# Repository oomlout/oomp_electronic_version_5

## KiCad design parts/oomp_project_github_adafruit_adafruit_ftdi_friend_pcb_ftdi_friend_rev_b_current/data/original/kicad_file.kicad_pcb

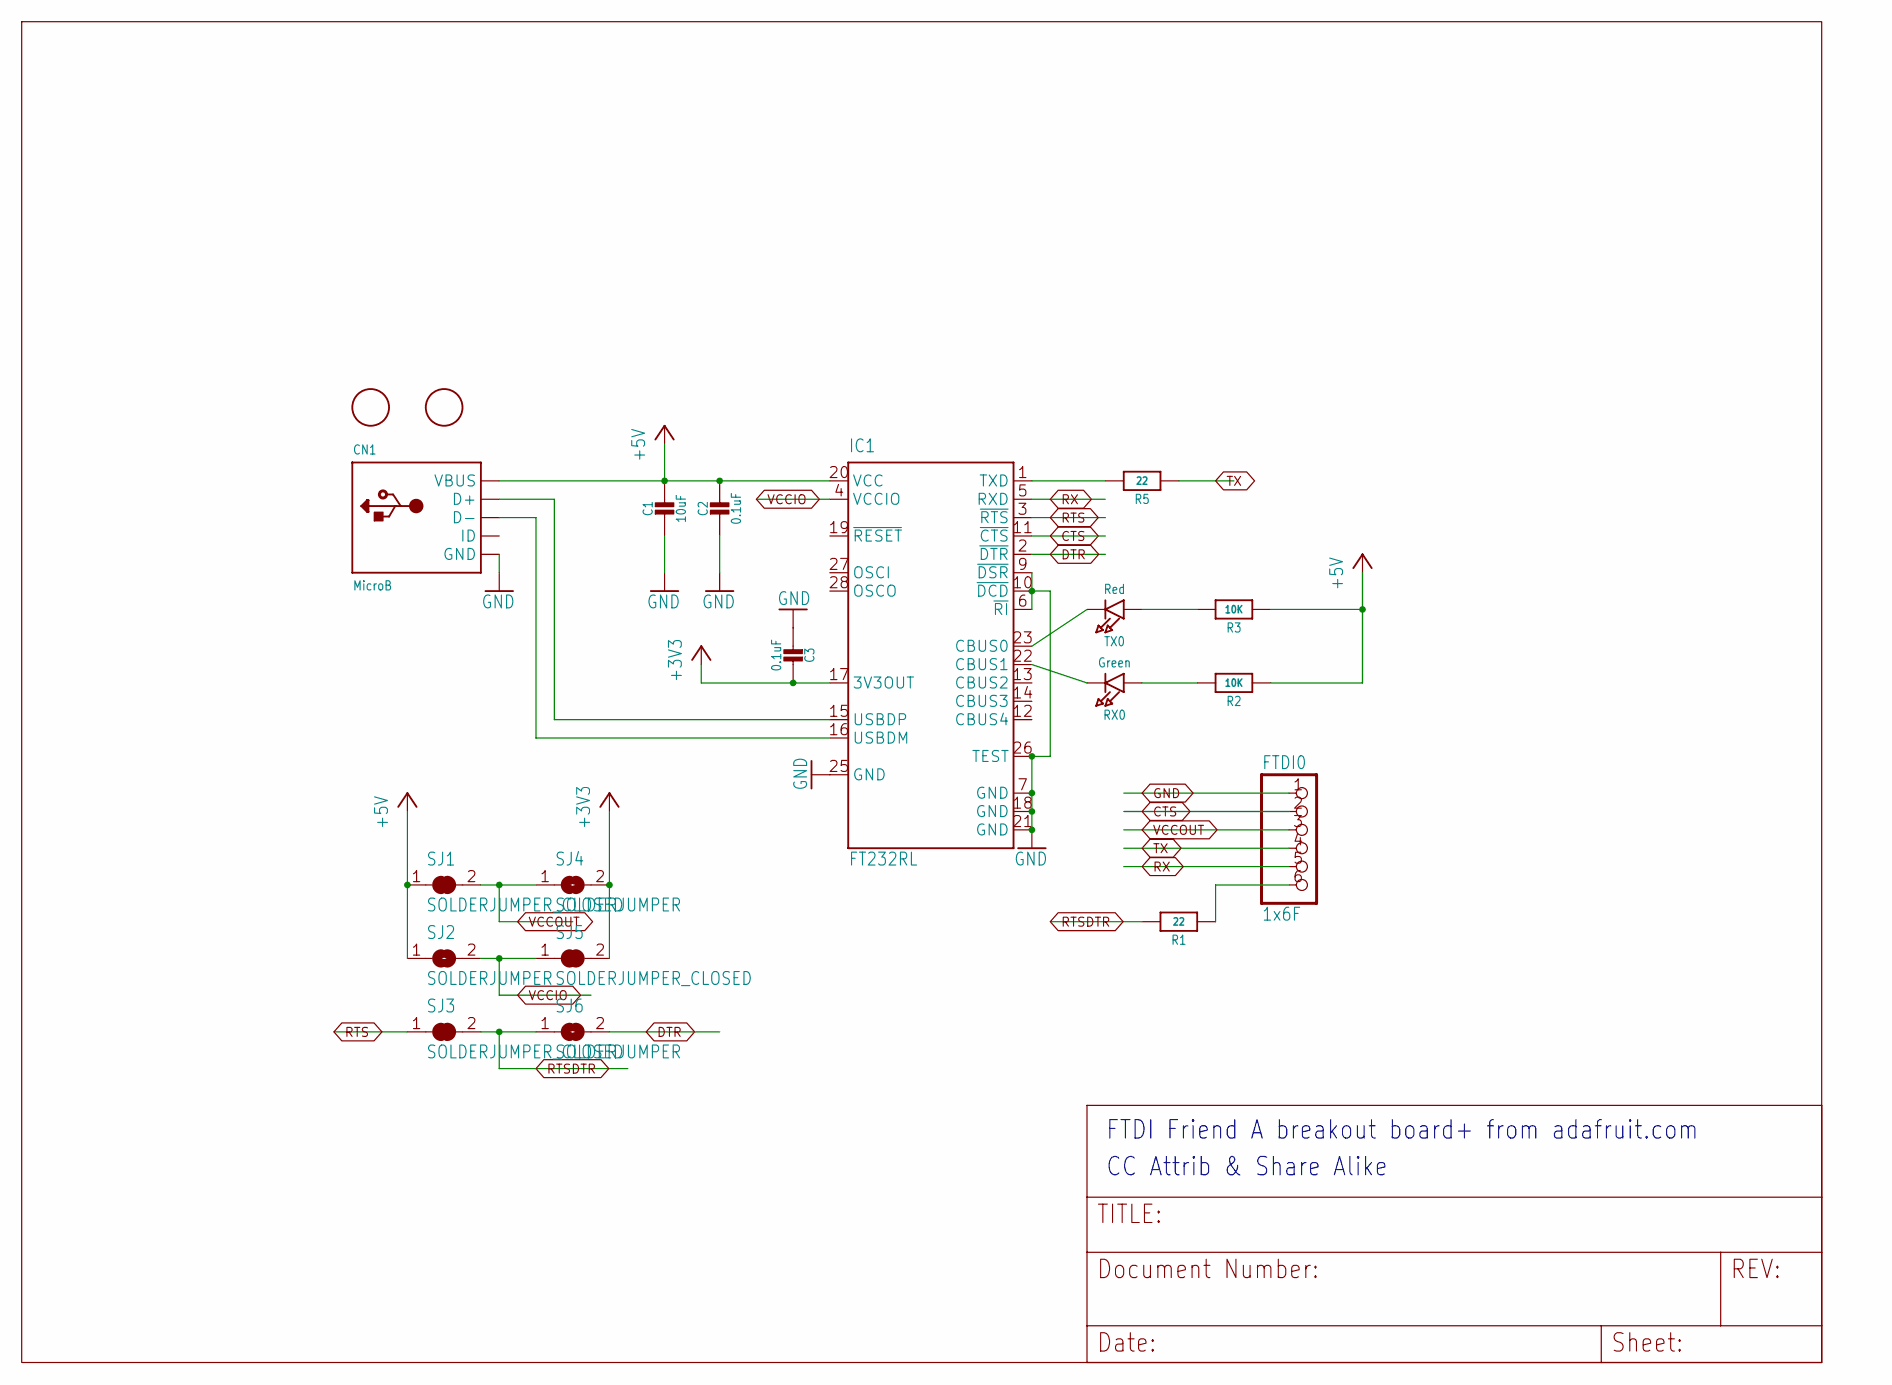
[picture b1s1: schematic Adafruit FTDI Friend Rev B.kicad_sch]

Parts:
C1: 10uF; 0805-NO
C2, C3: 0.1uF; 0603-NO
CN1: MicroB; SHOU_MICROXNJ073; LCSC C404969
FTDI0: 1x6F; 1X06-CLEANBIG
IC1: FT232RL; SSOP28; MPN FT232RL
R1, R5: 22; 0603-NO
R2, R3: 10K; 0603-NO
RX0: Green; CHIPLED_0603_NOOUTLINE
SJ1, SJ3, SJ5: SOLDERJUMPER_CLOSED; SOLDERJUMPER_CLOSEDWIRE
SJ2, SJ4, SJ6: SOLDERJUMPER; SOLDERJUMPER_ARROW_NOPASTE
TX0: Red; CHIPLED_0603_NOOUTLINE
U$1, U$2: FIDUCIAL; FIDUCIAL_1MM

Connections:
+3V3: C3.1, IC1.17 (3V3OUT), SJ4.2, SJ5.2
+5V: C1.1, C2.1, CN1.VBUS, IC1.20 (VCC), R2.1, R3.1, SJ1.1, SJ2.1
CTS: FTDI0.2, IC1.11 (~CTS)
DTR: IC1.2 (~DTR), SJ6.2
GND: C1.2, C2.2, C3.2, CN1.BASE@1 (GND), CN1.BASE@2 (GND), CN1.GND, CN1.SPRT@1 (GND), CN1.SPRT@2 (GND), CN1.SPRT@3 (GND), CN1.SPRT@4 (GND), FTDI0.1, IC1.6 (~RI), IC1.7 (GND), IC1.9 (~DSR), IC1.10 (~DCD), IC1.18 (GND), IC1.21 (GND), IC1.25 (GND), IC1.26 (TEST)
unnamed: FTDI0.6, R1.1
unnamed: CN1.D+, IC1.15 (USBDP)
unnamed: CN1.D-, IC1.16 (USBDM)
unnamed: IC1.1 (TXD), R5.2
unnamed: IC1.23 (CBUS0), TX0.C
unnamed: IC1.22 (CBUS1), RX0.C
unnamed: R2.2, RX0.A
unnamed: R3.2, TX0.A
RTS: IC1.3 (~RTS), SJ3.1
RTSDTR: R1.2, SJ3.2, SJ6.1
RX: FTDI0.5, IC1.5 (RXD)
TX: FTDI0.4, R5.1
VCCIO: IC1.4 (VCCIO), SJ2.2, SJ5.1
VCCOUT: FTDI0.3, SJ1.2, SJ4.1

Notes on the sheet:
CC Attrib & Share Alike
FTDI Friend~{} A breakout board+ from adafruit.com

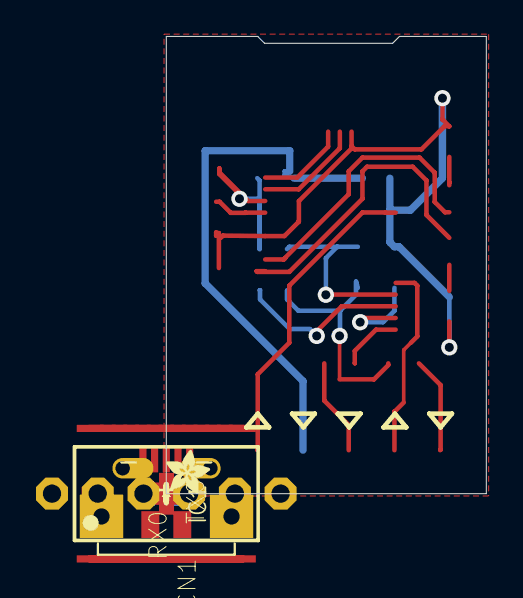
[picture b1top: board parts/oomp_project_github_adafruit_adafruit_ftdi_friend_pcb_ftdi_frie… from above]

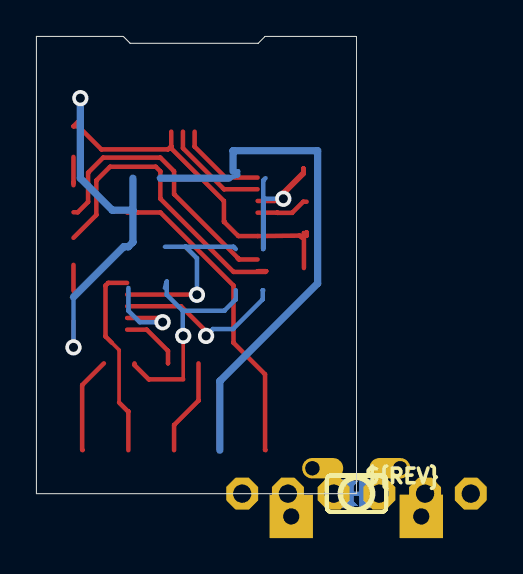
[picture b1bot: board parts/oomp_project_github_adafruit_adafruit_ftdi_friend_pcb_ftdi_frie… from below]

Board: 16 copper layers, 17.8 x 25.4 mm, 47 parts (21 on the bottom side), 19 nets.

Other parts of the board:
PLABEL0: PLABEL0
PLABEL1: PLABEL1
PLABEL2: PLABEL2
PLABEL3: PLABEL3
PLABEL4: PLABEL4
PLABEL5: PLABEL5
PLABEL6: PLABEL6
PLABEL7: PLABEL7
PLABEL8: PLABEL8
PLABEL9: PLABEL9
PLABEL10: PLABEL10
PLABEL11: PLABEL11
PLABEL12: PLABEL12
PLABEL13: PLABEL13
PLABEL14: PLABEL14
PLABEL15: PLABEL15
PLABEL16: PLABEL16
PLABEL17: PLABEL17
PLABEL18: PLABEL18
PLABEL19: PLABEL19
PLABEL20: PLABEL20
PLABEL21: PLABEL21
PLABEL22: PLABEL22
PLABEL23: PLABEL23
PLABEL24: PLABEL24
U$3: PCBFEAT-REV-040
U$4: ADAFRUIT_2.5MM

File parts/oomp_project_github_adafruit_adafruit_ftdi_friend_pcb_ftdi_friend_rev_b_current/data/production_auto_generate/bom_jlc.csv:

Comment,Designator,Footprint,LCSC Part #
,U$4,Adafruit FTDI Friend Rev B-import-fps:ADAFRUIT_2.5MM,
,U$3,Adafruit FTDI Friend Rev B-import-fps:PCBFEAT-REV-040,
,PLABEL0,Adafruit FTDI Friend Rev B-import-fps:PLABEL0,
,PLABEL1,Adafruit FTDI Friend Rev B-import-fps:PLABEL1,
,PLABEL10,Adafruit FTDI Friend Rev B-import-fps:PLABEL10,
,PLABEL11,Adafruit FTDI Friend Rev B-import-fps:PLABEL11,
,PLABEL12,Adafruit FTDI Friend Rev B-import-fps:PLABEL12,
,PLABEL13,Adafruit FTDI Friend Rev B-import-fps:PLABEL13,
,PLABEL14,Adafruit FTDI Friend Rev B-import-fps:PLABEL14,
,PLABEL15,Adafruit FTDI Friend Rev B-import-fps:PLABEL15,
,PLABEL16,Adafruit FTDI Friend Rev B-import-fps:PLABEL16,
,PLABEL17,Adafruit FTDI Friend Rev B-import-fps:PLABEL17,
,PLABEL18,Adafruit FTDI Friend Rev B-import-fps:PLABEL18,
,PLABEL19,Adafruit FTDI Friend Rev B-import-fps:PLABEL19,
,PLABEL2,Adafruit FTDI Friend Rev B-import-fps:PLABEL2,
,PLABEL20,Adafruit FTDI Friend Rev B-import-fps:PLABEL20,
,PLABEL21,Adafruit FTDI Friend Rev B-import-fps:PLABEL21,
,PLABEL22,Adafruit FTDI Friend Rev B-import-fps:PLABEL22,
,PLABEL23,Adafruit FTDI Friend Rev B-import-fps:PLABEL23,
,PLABEL24,Adafruit FTDI Friend Rev B-import-fps:PLABEL24,
,PLABEL3,Adafruit FTDI Friend Rev B-import-fps:PLABEL3,
,PLABEL4,Adafruit FTDI Friend Rev B-import-fps:PLABEL4,
,PLABEL5,Adafruit FTDI Friend Rev B-import-fps:PLABEL5,
,PLABEL6,Adafruit FTDI Friend Rev B-import-fps:PLABEL6,
,PLABEL7,Adafruit FTDI Friend Rev B-import-fps:PLABEL7,
,PLABEL8,Adafruit FTDI Friend Rev B-import-fps:PLABEL8,
,PLABEL9,Adafruit FTDI Friend Rev B-import-fps:PLABEL9,
0.1uF,"C2,C3",Adafruit FTDI Friend Rev B-import-fps:0603-NO,C14663
10K,"R2,R3",Adafruit FTDI Friend Rev B-import-fps:0603-NO,C98220
10uF,C1,Adafruit FTDI Friend Rev B-import-fps:0805-NO,
1x6F,FTDI0,Adafruit FTDI Friend Rev B-import-fps:1X06-CLEANBIG,C37208
22,"R1,R5",Adafruit FTDI Friend Rev B-import-fps:0603-NO,C23345
FIDUCIAL,"U$1,U$2",Adafruit FTDI Friend Rev B-import-fps:FIDUCIAL_1MM,
FT232RL,IC1,Adafruit FTDI Friend Rev B-import-fps:SSOP28,
Green,RX0,Adafruit FTDI Friend Rev B-import-fps:CHIPLED_0603_NOOUTLINE,
MicroB,CN1,Adafruit FTDI Friend Rev B-import-fps:SHOU_MICROXNJ073,
Red,TX0,Adafruit FTDI Friend Rev B-import-fps:CHIPLED_0603_NOOUTLINE,

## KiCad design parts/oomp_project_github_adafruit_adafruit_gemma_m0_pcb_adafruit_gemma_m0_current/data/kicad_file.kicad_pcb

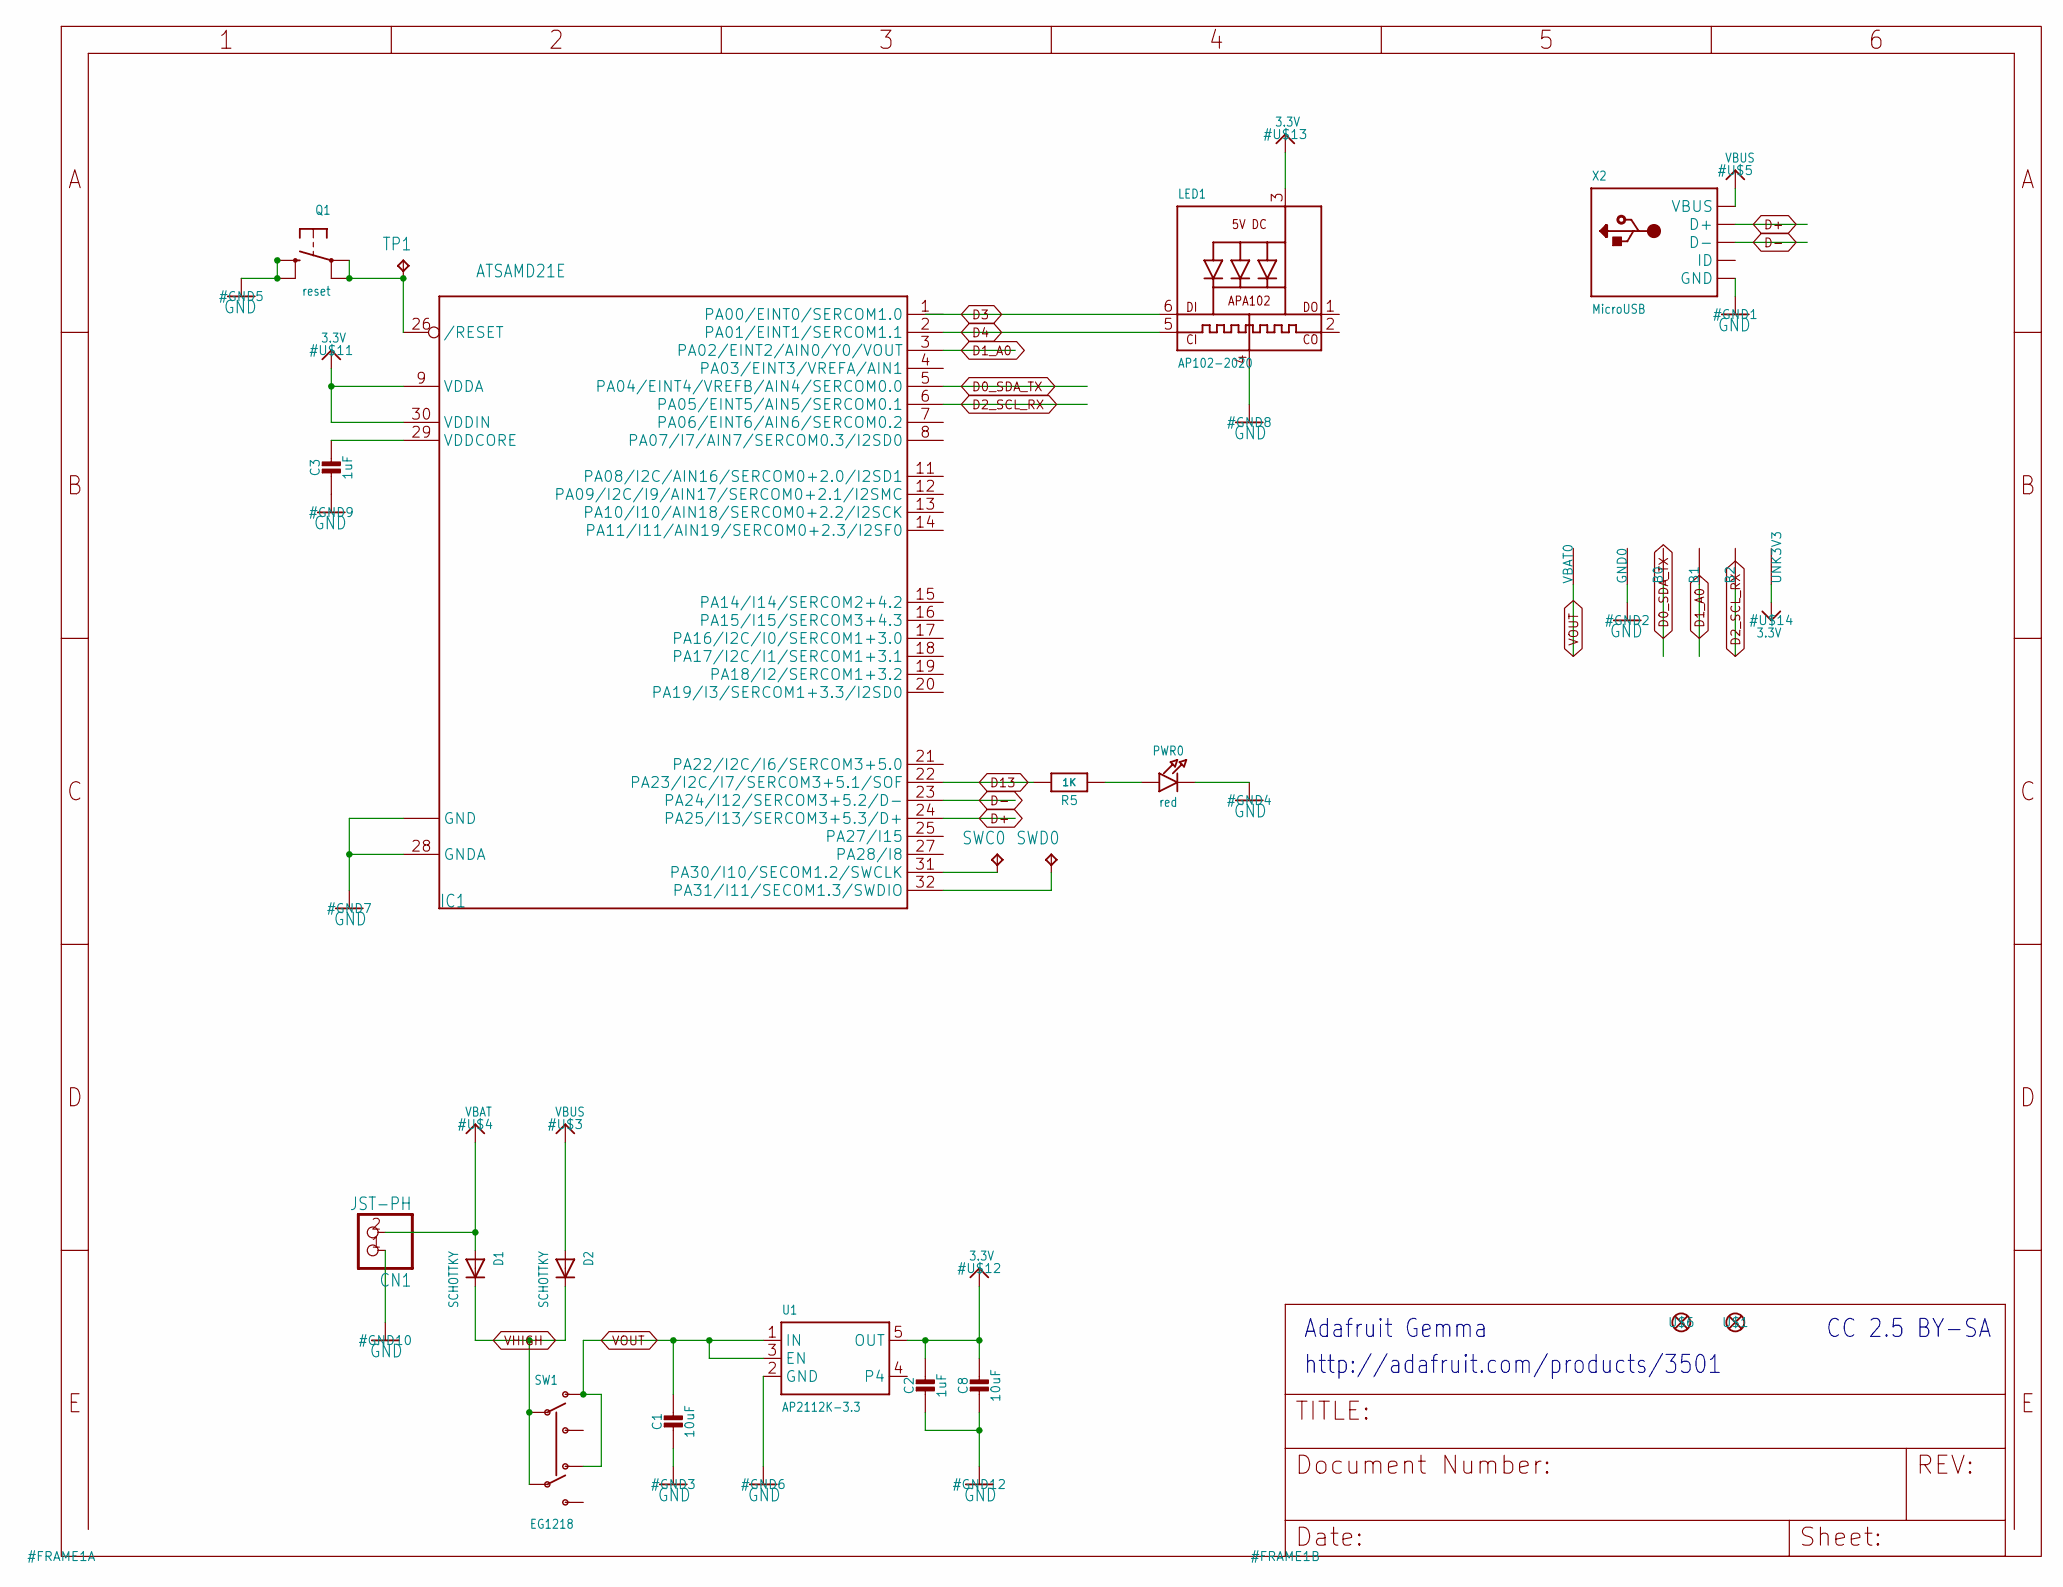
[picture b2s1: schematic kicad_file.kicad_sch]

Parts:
B0, B1, B2: SEWTAP-ALLIGATOR; SEWALLI
C1, C8: 10uF; 0805-NO
C2, C3: 1uF; 0603-NO
CN1: JST-PH; JSTPH2
D1, D2: SCHOTTKY; SOD-123FL
GND0: SEWTAP-ALLIGATOR; SEWALLI
IC1: ATSAMD21E; QFN32_5MM
LED1: AP102-2020; APA102_2020
PWR0: red; CHIPLED_0603_NOOUTLINE
Q1: reset; BTN_KMR2_4.6X2.8
R5: 1K; 0603-NO
SW1: EG1218; EG1390
SWC0: TPTP15R; TP15R
SWD0: TPTP15R; TP15R
TP1: TPTP16R; TP16R
U1: AP2112K-3.3; SOT23-5
U$1, U$6: FIDUCIAL_1MM
UNK3V3: SEWTAP-ALLIGATOR; SEWALLI
VBAT0: SEWTAP-ALLIGATOR; SEWALLI
X2: MicroUSB; 4UCONN_20329_V2

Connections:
3.3V: C2.1, C8.1, IC1.9 (VDDA), IC1.30 (VDDIN), LED1.3 (VDD), U1.5 (OUT), UNK3V3.P$1
D0_SDA_TX: B0.P$1, IC1.5 (PA04/EINT4/VREFB/AIN4/SERCOM0.0)
D1_A0: B1.P$1, IC1.3 (PA02/EINT2/AIN0/Y0/VOUT)
D2_SCL_RX: B2.P$1, IC1.6 (PA05/EINT5/AIN5/SERCOM0.1)
D3: IC1.1 (PA00/EINT0/SERCOM1.0), LED1.6 (DI)
D4: IC1.2 (PA01/EINT1/SERCOM1.1), LED1.5 (CKI)
D13: IC1.22 (PA23/I2C/I7/SERCOM3+5.1/SOF), R5.2
D+: IC1.24 (PA25/I13/SERCOM3+5.3/D+), X2.D+
D-: IC1.23 (PA24/I12/SERCOM3+5.2/D-), X2.D-
GND: C1.2, C2.2, C3.2, C8.2, CN1.1, GND0.P$1, IC1.10 (GND), IC1.28 (GNDA), IC1.33 (GND), LED1.4 (GND), PWR0.C, Q1.B (S), Q1.B' (S1), U1.2 (GND), X2.BASE@1 (GND), X2.BASE@2 (GND), X2.GND, X2.SPRT@1 (GND), X2.SPRT@2 (GND), X2.SPRT@3 (GND), X2.SPRT@4 (GND)
unnamed: PWR0.A, R5.1
SWCLK: IC1.31 (PA30/I10/SECOM1.2/SWCLK), SWC0.TP
SWDIO: IC1.32 (PA31/I11/SECOM1.3/SWDIO), SWD0.TP
VBAT: CN1.2, D1.A
VBUS: D2.A, X2.VBUS
VDDCORE: C3.1, IC1.29 (VDDCORE)
VHIGH: D1.C, D2.C, SW1.P1, SW1.P2
VOUT: C1.1, SW1.O1, SW1.O2, U1.1 (IN), U1.3 (EN), VBAT0.P$1
~RESET: IC1.26 (/RESET), Q1.A, Q1.A' (P1), TP1.TP

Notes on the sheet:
Adafruit Gemma
CC 2.5 BY-SA
http://adafruit.com/products/3501

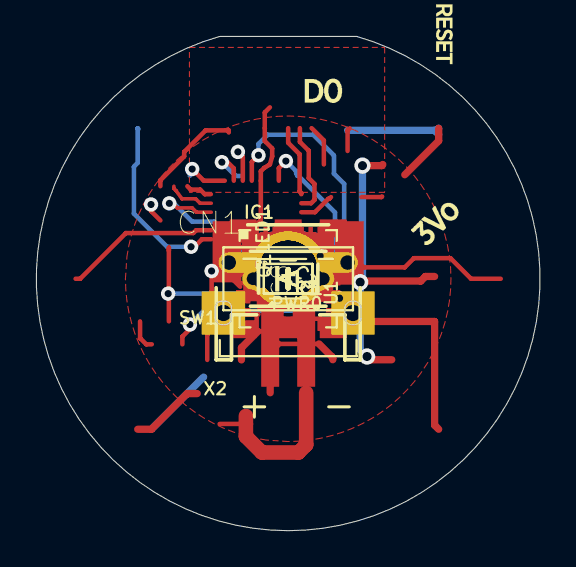
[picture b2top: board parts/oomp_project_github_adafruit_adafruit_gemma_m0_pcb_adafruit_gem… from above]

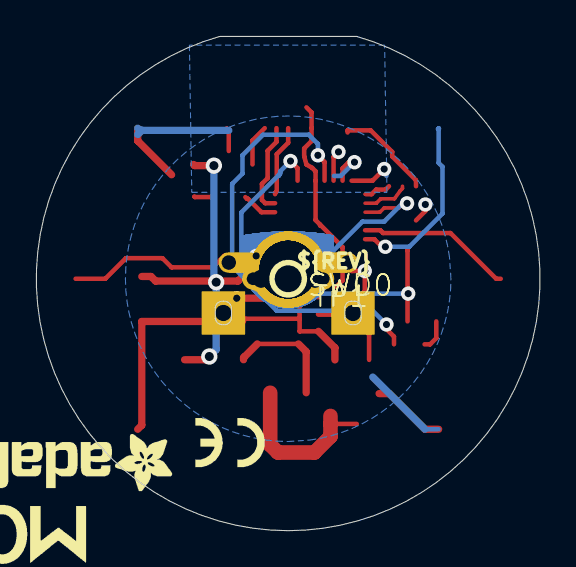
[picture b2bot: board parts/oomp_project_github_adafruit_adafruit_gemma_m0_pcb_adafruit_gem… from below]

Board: 16 copper layers, 28.0 x 27.5 mm, 29 parts (5 on the bottom side), 19 nets.

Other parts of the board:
U$7: GEMMA_M0_BOTTOM
U$8: GEMMA_M0_TOP
U$10: PCBFEAT-REV-040

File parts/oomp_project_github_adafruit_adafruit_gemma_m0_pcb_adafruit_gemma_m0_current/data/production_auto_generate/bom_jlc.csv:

Comment,Designator,Footprint,LCSC Part #
,U$7,Adafruit Gemma M0-import-fps:GEMMA_M0_BOTTOM,
,U$8,Adafruit Gemma M0-import-fps:GEMMA_M0_TOP,
,U$10,Adafruit Gemma M0-import-fps:PCBFEAT-REV-040,
10uF,"C1,C8",Adafruit Gemma M0-import-fps:0805-NO,
1K,R5,Adafruit Gemma M0-import-fps:0603-NO,C2907002
1uF,"C2,C3",Adafruit Gemma M0-import-fps:0603-NO,C5673
AP102-2020,LED1,Adafruit Gemma M0-import-fps:APA102_2020,
AP2112K-3.3,U1,Adafruit Gemma M0-import-fps:SOT23-5,
ATSAMD21E,IC1,Adafruit Gemma M0-import-fps:QFN32_5MM,
EG1218,SW1,Adafruit Gemma M0-import-fps:EG1390,
FIDUCIAL_1MM,"U$1,U$6",Adafruit Gemma M0-import-fps:FIDUCIAL_1MM,
JST-PH,CN1,Adafruit Gemma M0-import-fps:JSTPH2,
MicroUSB,X2,Adafruit Gemma M0-import-fps:4UCONN_20329_V2,
red,PWR0,Adafruit Gemma M0-import-fps:CHIPLED_0603_NOOUTLINE,
reset,Q1,Adafruit Gemma M0-import-fps:BTN_KMR2_4.6X2.8,
SCHOTTKY,"D1,D2",Adafruit Gemma M0-import-fps:SOD-123FL,
TPTP15R,"SWC0,SWD0",Adafruit Gemma M0-import-fps:TP15R,
TPTP16R,TP1,Adafruit Gemma M0-import-fps:TP16R,

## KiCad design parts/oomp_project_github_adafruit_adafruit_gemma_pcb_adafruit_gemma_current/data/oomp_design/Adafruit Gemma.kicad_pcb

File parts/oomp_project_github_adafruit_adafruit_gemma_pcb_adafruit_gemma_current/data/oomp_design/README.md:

# OOMP KiCad design copy

Open `Adafruit Gemma.kicad_pro` (or the `.kicad_pcb` / `.kicad_sch`) in KiCad. Local OOMP libraries are under `libraries/`. Original inputs are preserved in [../original/](../original/).

Only verified unchanged installed KiCad defaults were renamed. Modified, custom, unmatched and unavailable items remain unchanged. Soldering variants are never swapped during conversion. Existing pad coordinates, nets and UUIDs are preserved.

See [conversion_report.yaml](conversion_report.yaml) for every conversion and skip. Copy this directory before editing; regeneration refuses to overwrite edited design files.

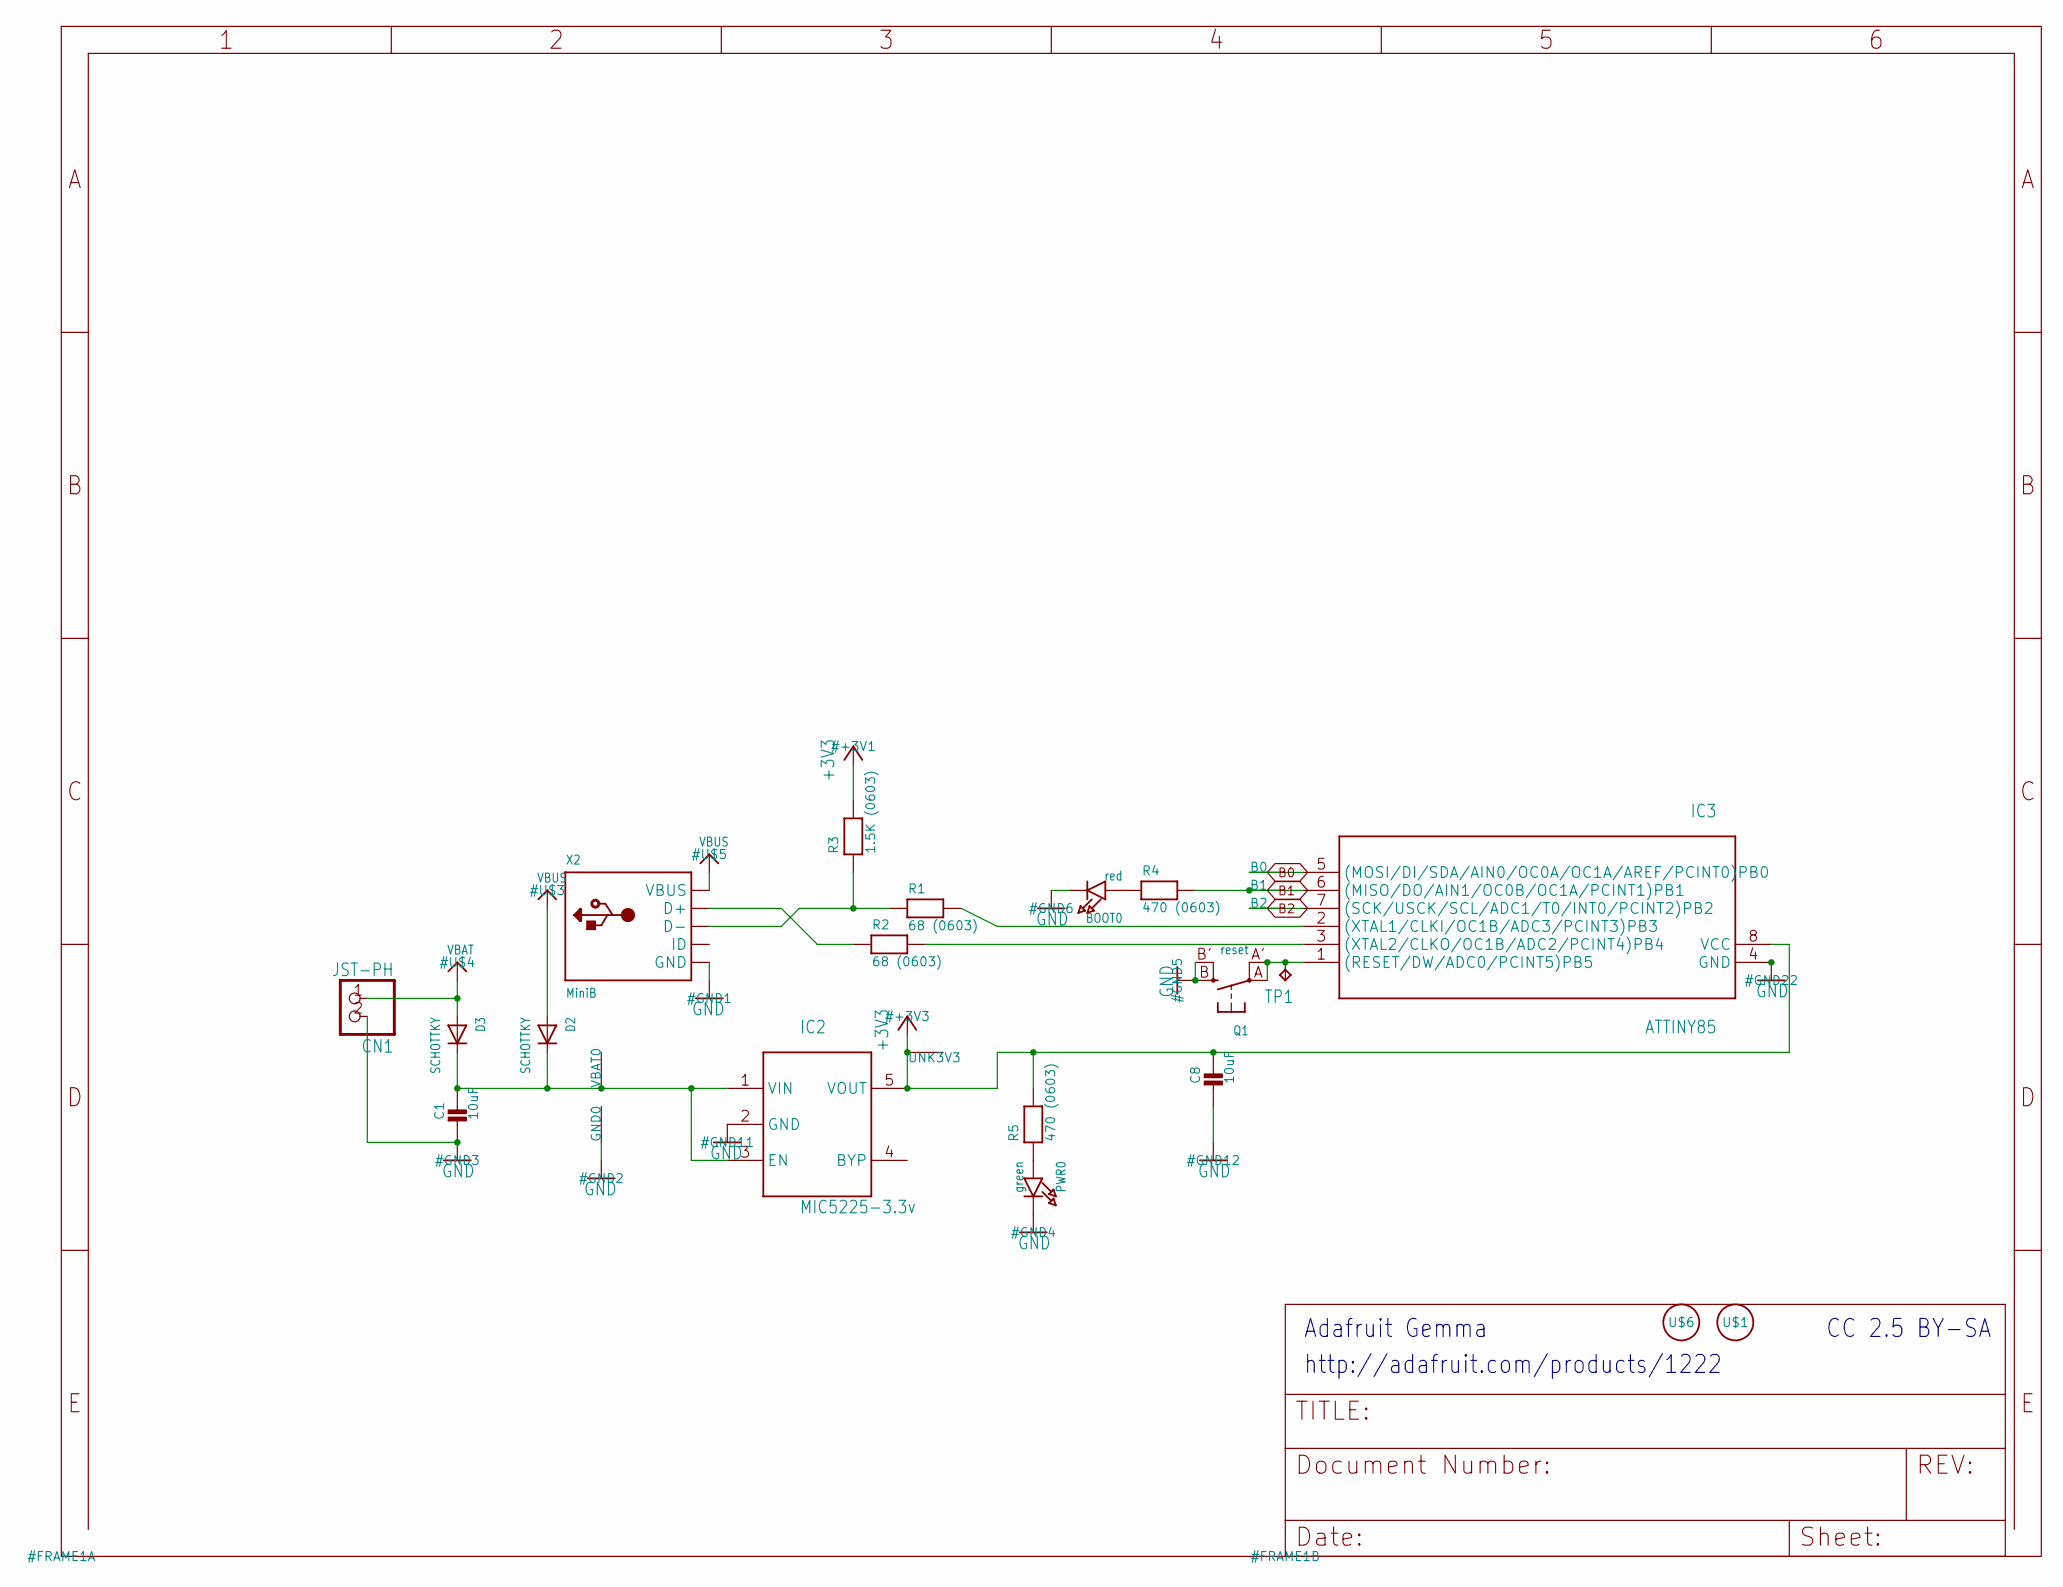
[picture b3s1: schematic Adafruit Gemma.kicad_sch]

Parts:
B0, B1, B2: SEWTAP-2.0IN; SEWINGTAP_2.0
BOOT0: red; CHIPLED_0805_NOOUTLINE
C1, C8: 10uF; 0805-NO
CN1: JST-PH; JST-PH-2-SMT-RA
D2, D3: SCHOTTKY; SOD-123FL
GND0: SEWTAP-2.0IN; SEWINGTAP_2.0
IC2: MIC5225-3.3v; SOT23-5L
IC3: ATTINY85; SOIC8
PWR0: green; CHIPLED_0805_NOOUTLINE
Q1: reset; BTN_KMR2_4.6X2.8
R1, R2: 68 (0603); 0603-NO
R3: 1.5K (0603); 0603-NO
R4, R5: 470 (0603); 0603-NO
TP1: TPB2,54; B2,54
U$1, U$6: FIDUCIAL; FIDUCIAL_1MM
UNK3V3: SEWTAP-2.0IN; SEWINGTAP_2.0
VBAT0: SEWTAP-2.0IN; SEWINGTAP_2.0
X2: MiniB; USB-MINI_MEDIUM

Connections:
+3V3: C8.1, IC2.5 (VOUT), IC3.8 (VCC), R3.2, R5.2, UNK3V3.P$1
B0: B0.P$1, IC3.5 ((MOSI/DI/SDA/AIN0/OC0A/OC1A/AREF/PCINT0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)
B1: B1.P$1, IC3.6 ((MISO/DO/AIN1/OC0B/OC1A/PCINT1)PB1), R4.2
B2: B2.P$1, IC3.7 ((SCK/USCK/SCL/ADC1/T0/INT0/PCINT2)PB2)
GND: BOOT0.C, C1.2, C8.2, CN1.2 (1), GND0.P$1, IC2.2 (GND), IC3.4 (GND), PWR0.C, Q1.B (S), Q1.B' (S1), X2.GND, X2.GND1 (GND), X2.GND2 (GND), X2.GND3 (GND), X2.GND4 (GND)
unnamed: IC3.1 ((RESET/DW/ADC0/PCINT5)PB5), Q1.A, Q1.A' (P1), TP1.TP
unnamed: R2.1, X2.D+
unnamed: IC3.2 ((XTAL1/CLKI/OC1B/ADC3/PCINT3)PB3), R1.2
unnamed: IC3.3 ((XTAL2/CLKO/OC1B/ADC2/PCINT4)PB4), R2.2
unnamed: R1.1, R3.1, X2.D-
unnamed: BOOT0.A, R4.1
unnamed: C1.1, D2.C, D3.C, IC2.1 (VIN), IC2.3 (EN), VBAT0.P$1
unnamed: PWR0.A, R5.1
VBAT: CN1.1 (2), D3.A
VBUS: D2.A, X2.VBUS

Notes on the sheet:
http://adafruit.com/products/1222
Adafruit Gemma
CC 2.5 BY-SA

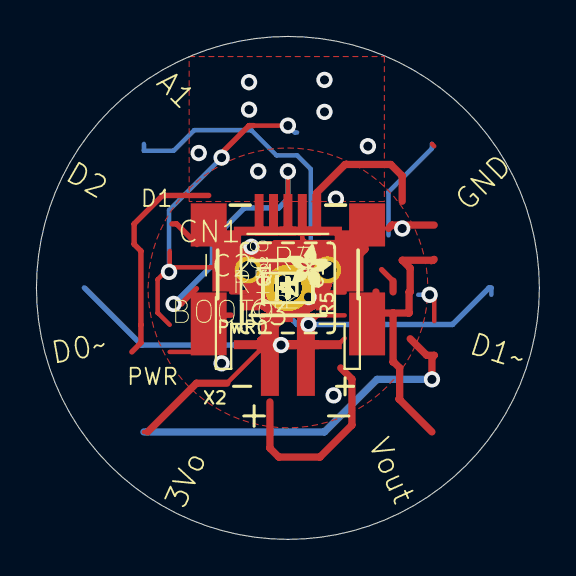
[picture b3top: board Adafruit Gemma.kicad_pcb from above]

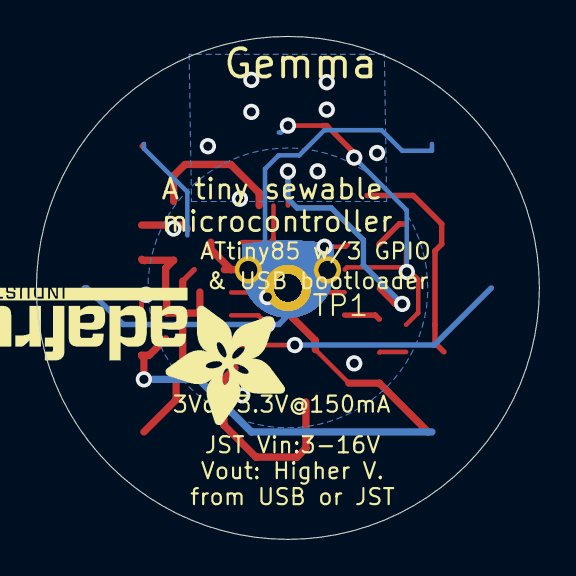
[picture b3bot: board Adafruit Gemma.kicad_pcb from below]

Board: 16 copper layers, 27.9 x 27.9 mm, 27 parts (2 on the bottom side), 15 nets.

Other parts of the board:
U$2: ADAFRUIT_2.5MM
U$7: ADAFRUIT_TEXT_20MM

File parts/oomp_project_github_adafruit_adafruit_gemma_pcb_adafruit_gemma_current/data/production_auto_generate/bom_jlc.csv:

Comment,Designator,Footprint,LCSC Part #
,U$2,Adafruit Gemma-import-fps:ADAFRUIT_2.5MM,
,U$7,Adafruit Gemma-import-fps:ADAFRUIT_TEXT_20MM,
1.5K (0603),R3,Adafruit Gemma-import-fps:0603-NO,C2930050
10uF,"C1,C8",Adafruit Gemma-import-fps:0805-NO,
470 (0603),"R4,R5",Adafruit Gemma-import-fps:0603-NO,C23179
68 (0603),"R1,R2",Adafruit Gemma-import-fps:0603-NO,C27592
ATTINY85,IC3,Adafruit Gemma-import-fps:SOIC8,
FIDUCIAL,"U$1,U$6",Adafruit Gemma-import-fps:FIDUCIAL_1MM,
green,PWR0,Adafruit Gemma-import-fps:CHIPLED_0805_NOOUTLINE,
JST-PH,CN1,Adafruit Gemma-import-fps:JST-PH-2-SMT-RA,
MIC5225-3.3v,IC2,Adafruit Gemma-import-fps:SOT23-5L,
MiniB,X2,Adafruit Gemma-import-fps:USB-MINI_MEDIUM,
red,BOOT0,Adafruit Gemma-import-fps:CHIPLED_0805_NOOUTLINE,
reset,Q1,Adafruit Gemma-import-fps:BTN_KMR2_4.6X2.8,
SCHOTTKY,"D2,D3",Adafruit Gemma-import-fps:SOD-123FL,
"TPB2,54",TP1,"Adafruit Gemma-import-fps:B2,54",

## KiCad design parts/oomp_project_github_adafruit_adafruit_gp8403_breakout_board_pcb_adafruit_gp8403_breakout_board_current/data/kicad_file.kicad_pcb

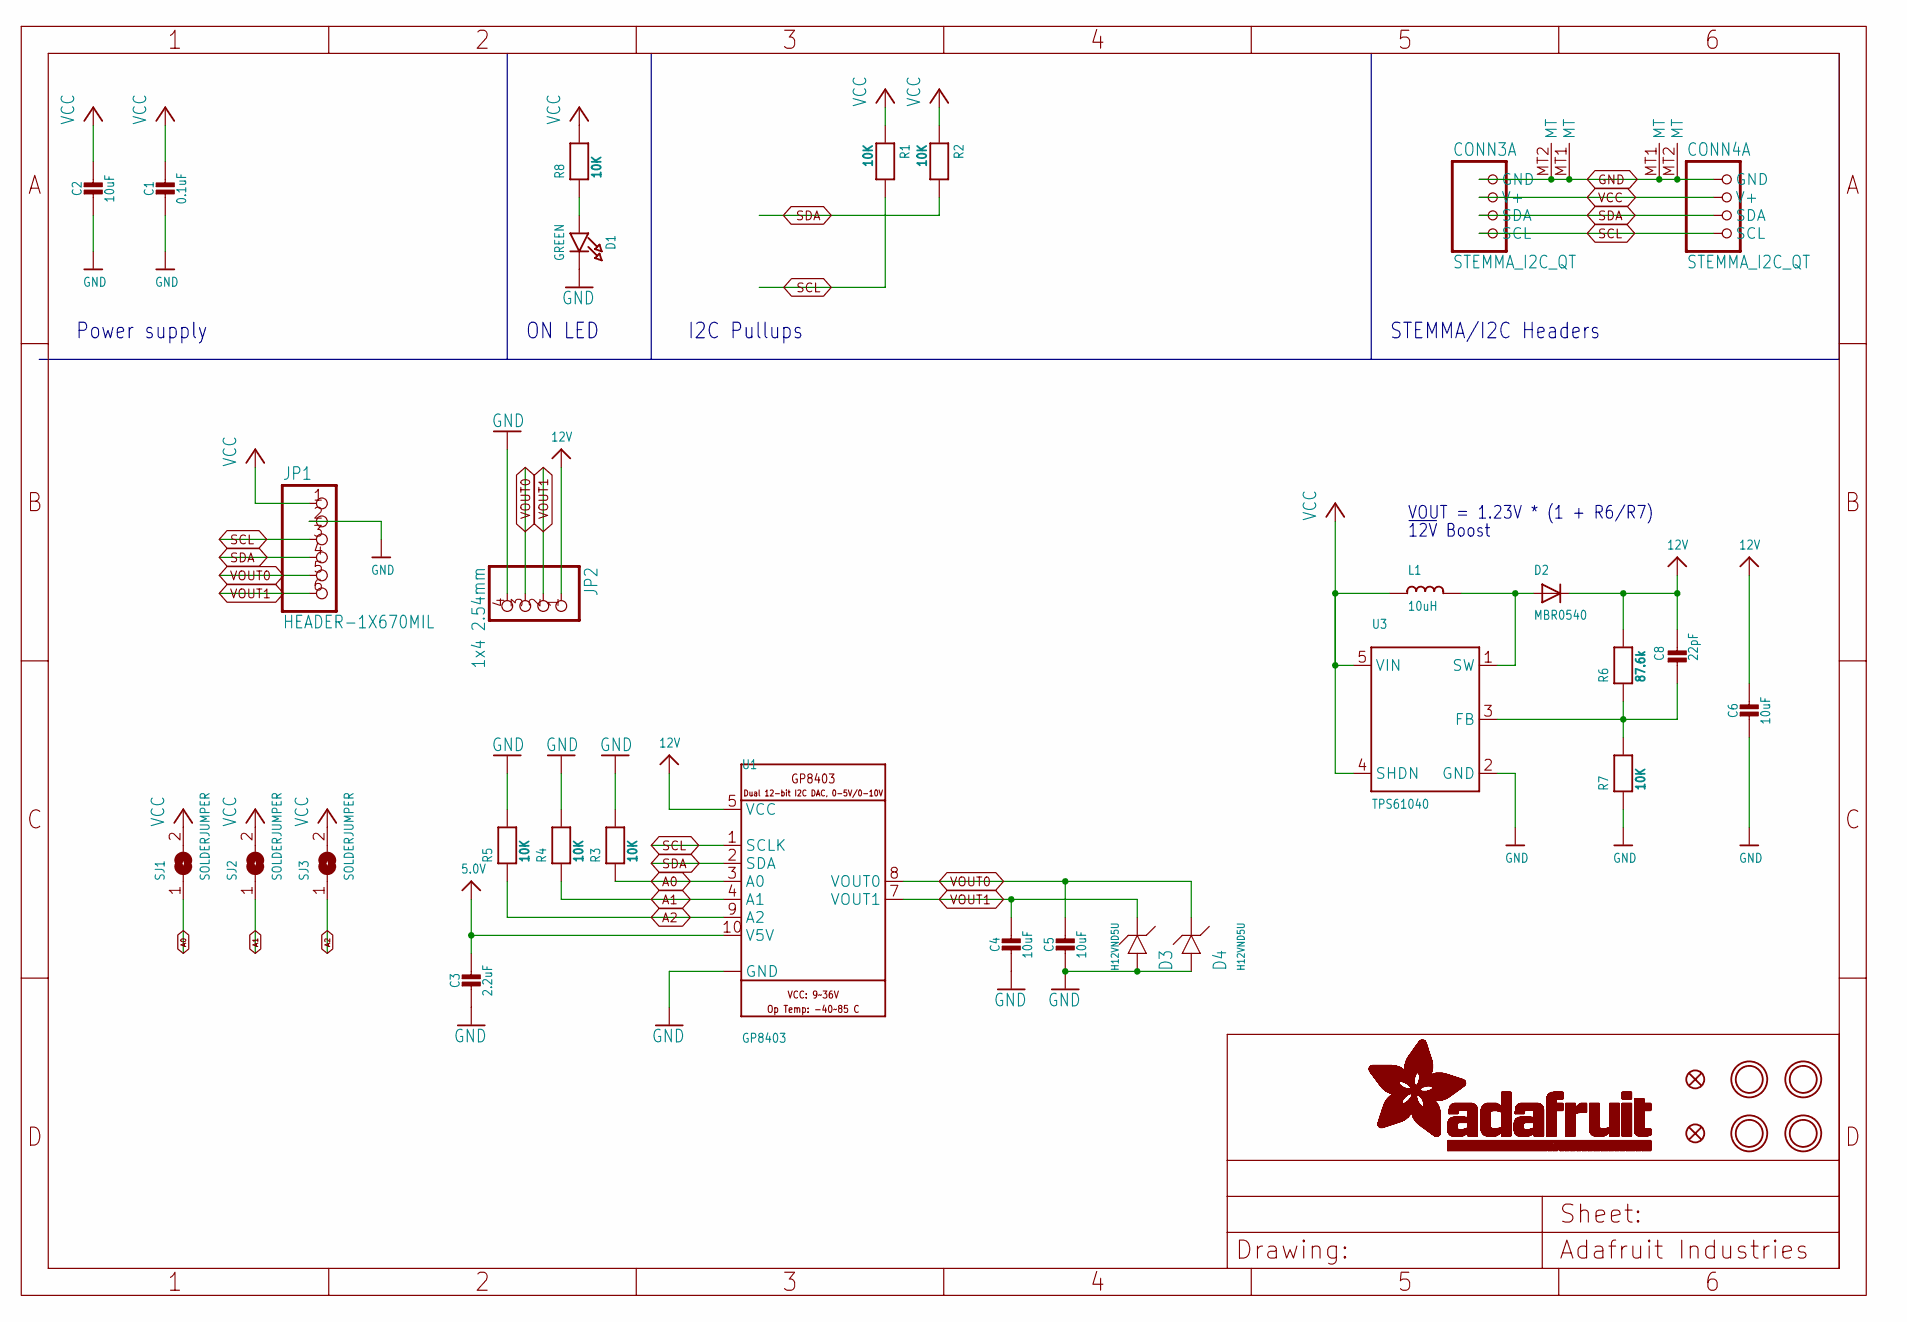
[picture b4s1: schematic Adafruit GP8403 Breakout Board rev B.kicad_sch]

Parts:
C1: 0.1uF; 0603-NO
C2, C4, C5, C6: 10uF; 0805-NO
C3: 2.2uF; 0603-NO
C8: 22pF; 0603-NO
CONN3, CONN4: STEMMA_I2C_QT; JST_SH4; LCSC C2905006
D1: GREEN; CHIPLED_0603_NOOUTLINE
D2: MBR0540; SOD-123FL
D3, D4: H12VND5U; SOD-523
FID3, FID4: FIDUCIAL_0.5MM
JP1: HEADER-1X670MIL; 1X06_ROUND_70
JP2: 1x4 2.54mm; 1X04_2.54MMTERMINAL
L1: 10uH; INDUCTOR_1007
R1, R2, R3, R4, R5, R7, R8: 10K; 0603-NO
R6: 87.6k; 0603-NO
SJ1, SJ2, SJ3: SOLDERJUMPER; SOLDERJUMPER_ARROW_NOPASTE
U1: GP8403; ESSOP10-EP
U3: TPS61040; SOT23-5
U$1, U$17, U$19, U$21: MOUNTINGHOLE2.5; MOUNTINGHOLE_2.5_PLATED

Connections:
5.0V: C3.1, U1.10 (V5V)
12V: C6.1, C8.1, D2.C, JP2.1, R6.2, U1.5 (VCC)
A0: R3.1, SJ1.1, U1.3 (A0)
A1: R4.1, SJ2.1, U1.4 (A1)
A2: R5.1, SJ3.1, U1.9 (A2)
GND: C1.2, C2.2, C3.2, C4.2, C5.2, C6.2, CONN3.1 (GND), CONN3.MT1 (MT), CONN3.MT2 (MT), CONN4.1 (GND), CONN4.MT1 (MT), CONN4.MT2 (MT), D1.C, D3.A, D4.A, JP1.2, JP2.4, R3.2, R4.2, R5.2, R7.1, U1.6 (GND), U1.EP (GND), U3.2 (GND)
unnamed: D1.A, R8.1
unnamed: D2.A, L1.P$2 (2), U3.1 (SW)
unnamed: C8.2, R6.1, R7.2, U3.3 (FB)
SCL: CONN3.4 (SCL), CONN4.4 (SCL), JP1.3, R1.2, U1.1 (SCLK)
SDA: CONN3.3 (SDA), CONN4.3 (SDA), JP1.4, R2.2, U1.2 (SDA)
VCC: C1.1, C2.1, CONN3.2 (V+), CONN4.2 (V+), JP1.1, L1.P$1 (1), R1.1, R2.1, R8.2, SJ1.2, SJ2.2, SJ3.2, U3.4 (SHDN), U3.5 (VIN)
VOUT0: C5.1, D4.K (C), JP1.5, JP2.3, U1.8 (VOUT0)
VOUT1: C4.1, D3.K (C), JP1.6, JP2.2, U1.7 (VOUT1)

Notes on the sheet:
Power supply
ON LED
~{12V} Boost
STEMMA/I2C Headers
I2C Pullups
VOUT = 1.23V * (1 + R6/R7)
